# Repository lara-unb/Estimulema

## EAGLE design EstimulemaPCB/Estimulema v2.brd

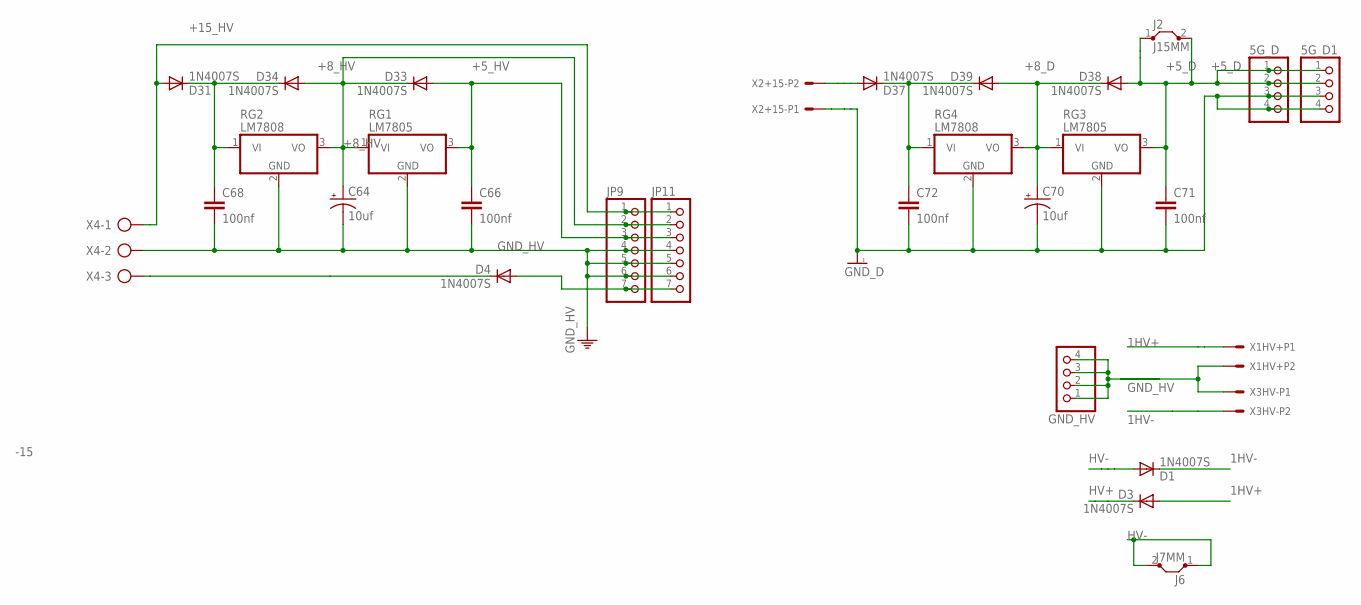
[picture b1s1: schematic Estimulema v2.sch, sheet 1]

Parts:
5G_D, 5G_D1: PINHD-1X4; 1X04
C64, C70: 10uf; E2-5
C66, C68, C71, C72: 100nf; C025-025X050
D1, D3, D4, D31, D33, D34, D37, D38, D39: 1N4007S; RESM4226X229
GND_HV: PINHD-1X4; 1X04
J2: J15MM; 15
J6: J7MM; 07
JP9, JP11: PINHD-1X7; 1X07
RG1, RG3: LM7805; TO220V
RG2, RG4: LM7808; TO220V
X1HV+, X2+15-, X3HV-: CONECTOR_5.08; CONECTOR_X2_5.08
X4: AK300/3

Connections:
1HV+: D3.AN (A), X1HV+.1
1HV-: D1.CA (C), X3HV-.2
+5_D: 5G_D.1, 5G_D.2, 5G_D1.1, 5G_D1.2, C71.1, D38.AN (A), J2.1, J2.2, RG3.3 (VO); also elsewhere on the board
+5_HV: C66.1, D33.AN (A), JP9.3, JP11.3, RG1.3 (VO); also elsewhere on the board
+8_D: C70.+, D38.CA (C), D39.AN (A), RG3.1 (VI), RG4.3 (VO)
+8_HV: C64.+, D33.CA (C), D34.AN (A), JP9.2, JP11.2, RG1.1 (VI), RG2.3 (VO)
+15_HV: D31.AN (A), JP9.1, JP11.1, X4.1; also elsewhere on the board
-15: D4.CA (C), X4.3
-15_HV: D4.AN (A), JP9.7, JP11.7; also elsewhere on the board
GND_D: 5G_D.3, 5G_D.4, 5G_D1.3, 5G_D1.4, C70.-, C71.2, C72.2, RG3.2 (GND), RG4.2 (GND), X2+15-.1; also elsewhere on the board
GND_HV: C64.-, C66.2, C68.2, GND_HV.1, GND_HV.2, GND_HV.3, GND_HV.4, JP9.4, JP9.5, JP9.6, JP11.4, JP11.5, JP11.6, RG1.2 (GND), RG2.2 (GND), X1HV+.2, X3HV-.1, X4.2; also elsewhere on the board
HV+: D3.CA (C); also elsewhere on the board
HV-: D1.AN (A), J6.1, J6.2; also elsewhere on the board
unnamed: D37.AN (A), X2+15-.2
unnamed: C68.1, D31.CA (C), D34.CA (C), RG2.1 (VI)
unnamed: C72.1, D37.CA (C), D39.CA (C), RG4.1 (VI)

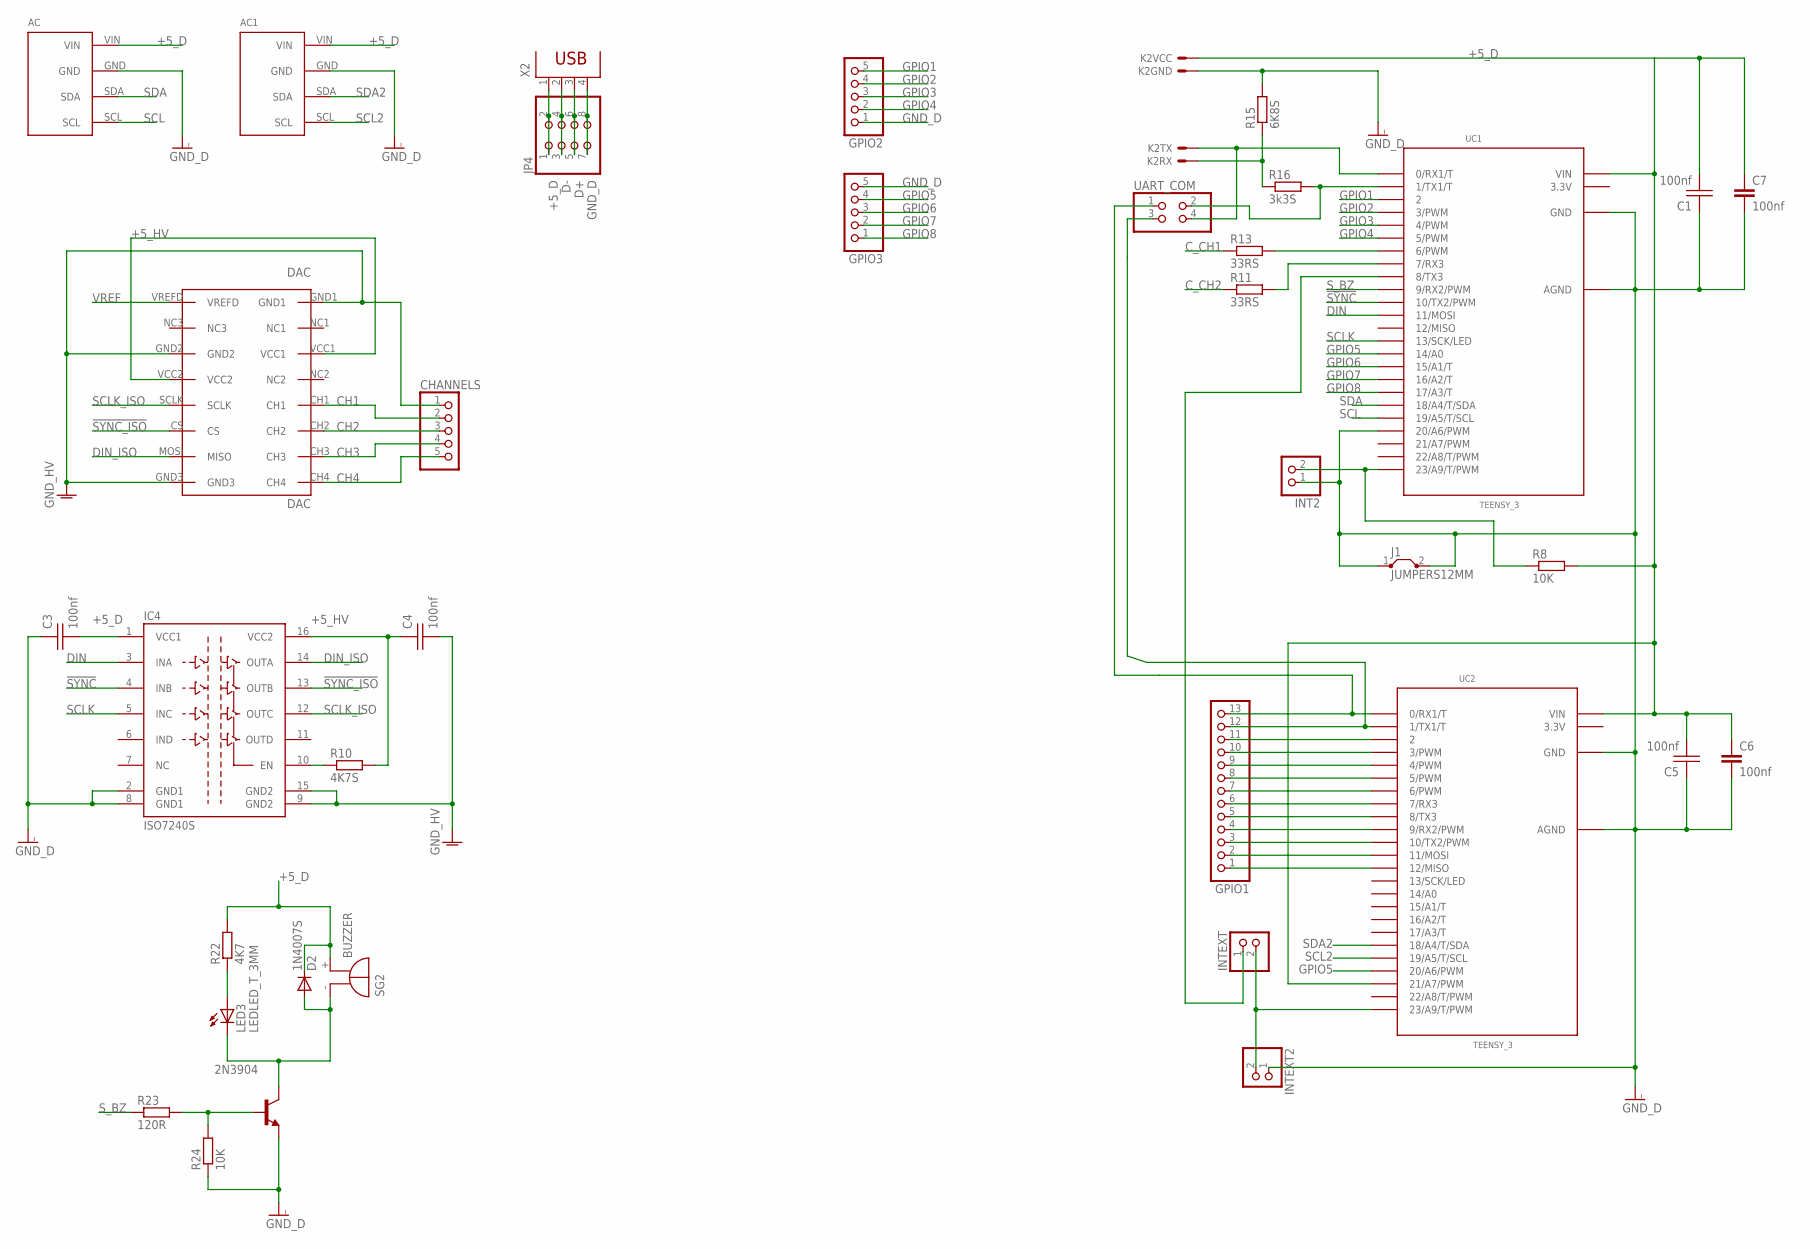
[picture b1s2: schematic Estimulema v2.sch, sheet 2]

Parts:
2N3904: 29-NPN-TO92-EBC; TO92-EBC
AC: CONECTOR_ACELEROMETRO_MPU6050CONECTOR_MPU6050; MPU6050
AC1: MPU6050
C1, C3, C4, C5: 100nf; CAP_CER_SMD-0805
C6, C7: 100nf; C025-025X050
CHANNELS: PINHD-1X5; 1X05
D2: 1N4007S; RESM4226X229
DAC: DAC; DACMOD_P
GPIO1: PINHD-1X13; 1X13
GPIO2, GPIO3: PINHD-1X5; 1X05
IC4: ISO7240S; SO-16DW
INT2: PINHD-1X2; 1X02
INTEXT, INTEXT2: PINHD-1X2; 1X02
J1: JUMPERS12MM; 12
JP4: PINHD-2X4; 2X04
K2: HC-06; CONECTOR_BTHC-06
LED3: LEDLED_T_3MM; LED3MM
R8, R24: 10K; RESISTENCIA_0805
R10: 4K7S; RESISTENCIA_0805
R11, R13: 33RS; RESISTENCIA_0805
R15: 6K8S; RESISTENCIA_0805
R16: 3k3S; RESISTENCIA_0805
R22: 4K7; RESISTENCIA_0805
R23: 120R; RESISTENCIA_0805
SG2: BUZZER
UART_COM: PINHD-2X2; 2X02
UC1, UC2: TEENSY_3; TEENSY_3.0-3.2_DIL
X2: PN61729

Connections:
3.3V: UC1.3.3V, UC2.3.3V
!SYNC: IC4.4 (INB), UC1.10 (10/TX2/PWM)
!SYNC_ISO: DAC.CS, IC4.13 (OUTB)
+5_D: AC.VIN, AC1.VIN, C1.2, C3.2, C5.2, C6.1, C7.1, D2.CA (C), IC4.1 (VCC1), JP4.1, JP4.2, K2.1, R8.2, R22.2, SG2.+ (-), UC1.VIN, UC2.21/A7 (21/A7/PWM), UC2.VIN, X2.1; also elsewhere on the board
+5_HV: C4.1, DAC.VCC1, DAC.VCC2, IC4.16 (VCC2), R10.2; also elsewhere on the board
CH1: CHANNELS.2, DAC.CH1; also elsewhere on the board
CH2: CHANNELS.3, DAC.CH2; also elsewhere on the board
CH3: CHANNELS.4, DAC.CH3
CH4: CHANNELS.5, DAC.CH4
C_15D: GPIO1.11, UC2.2
C_CH1: R13.1; also elsewhere on the board
C_CH2: R11.1; also elsewhere on the board
D+: JP4.5, JP4.6, X2.3
D-: JP4.3, JP4.4, X2.2
DIN: IC4.3 (INA), UC1.11 (11/MOSI)
DIN_ISO: DAC.MOSI (MISO), IC4.14 (OUTA)
GNDI: C3.1, IC4.2 (GND1), IC4.8 (GND1)
GND_D: 2N3904.E, AC.GND, AC1.GND, C1.1, C5.1, C6.2, C7.2, GPIO2.1, GPIO3.5, INT2.1, INTEXT2.1, J1.1, J1.2, JP4.7, JP4.8, K2.2, R15.2, R24.1, UC1.20/A6 (20/A6/PWM), UC1.AGND, UC1.GND, UC2.AGND, UC2.GND, X2.4; also elsewhere on the board
GND_HV: C4.2, CHANNELS.1, DAC.GND1, DAC.GND2, DAC.GND3, IC4.9 (GND2), IC4.15 (GND2); also elsewhere on the board
GPIO1: GPIO2.5, UC1.2
GPIO2: GPIO2.4, UC1.3 (3/PWM)
GPIO3: GPIO2.3, UC1.4 (4/PWM)
GPIO4: GPIO2.2, UC1.5 (5/PWM)
GPIO5: GPIO3.4, UC1.14/A0, UC2.20/A6 (20/A6/PWM)
GPIO6: GPIO3.3, UC1.15/A1 (15/A1/T)
GPIO7: GPIO3.2, UC1.16/A2 (16/A2/T)
GPIO8: GPIO3.1, UC1.17/A3 (17/A3/T)
unnamed: INTEXT.2, INTEXT2.2, UC2.23/A9 (23/A9/T/PWM)
unnamed: INTEXT.1, UC1.8 (8/TX3)
unnamed: GPIO1.13, UART_COM.1, UC2.0 (0/RX1/T)
unnamed: GPIO1.12, UART_COM.3, UC2.1 (1/TX1/T)
unnamed: GPIO1.10, UC2.3 (3/PWM)
unnamed: GPIO1.9, UC2.4 (4/PWM)
unnamed: GPIO1.8, UC2.5 (5/PWM)
unnamed: GPIO1.7, UC2.6 (6/PWM)
unnamed: GPIO1.6, UC2.7 (7/RX3)
unnamed: GPIO1.5, UC2.8 (8/TX3)
unnamed: GPIO1.4, UC2.9 (9/RX2/PWM)
unnamed: GPIO1.3, UC2.10 (10/TX2/PWM)
unnamed: GPIO1.2, UC2.11 (11/MOSI)
unnamed: GPIO1.1, UC2.12 (12/MISO)
unnamed: R16.2, UART_COM.2, UC1.1 (1/TX1/T)
unnamed: K2.3, UART_COM.4, UC1.0 (0/RX1/T)
unnamed: IC4.10 (EN), R10.1
unnamed: R13.2, UC1.6 (6/PWM)
unnamed: R11.2, UC1.7 (7/RX3)
unnamed: K2.4, R15.1, R16.1
unnamed: LED3.A, R22.1
unnamed: 2N3904.C, D2.AN (A), LED3.K (C), SG2.- (+)
unnamed: 2N3904.B, R23.2, R24.2
unnamed: INT2.2, R8.1, UC1.23/A9 (23/A9/T/PWM)
SCL: AC.SCL, UC1.19/A5 (19/A5/T/SCL)
SCL2: AC1.SCL, UC2.19/A5 (19/A5/T/SCL)
SCLK: IC4.5 (INC), UC1.13 (13/SCK/LED)
SCLK_ISO: DAC.SCLK, IC4.12 (OUTC)
SDA: AC.SDA, UC1.18/A4 (18/A4/T/SDA)
SDA2: AC1.SDA, UC2.18/A4 (18/A4/T/SDA)
S_BZ: R23.1, UC1.9 (9/RX2/PWM)
VREF: DAC.VREFD; also elsewhere on the board

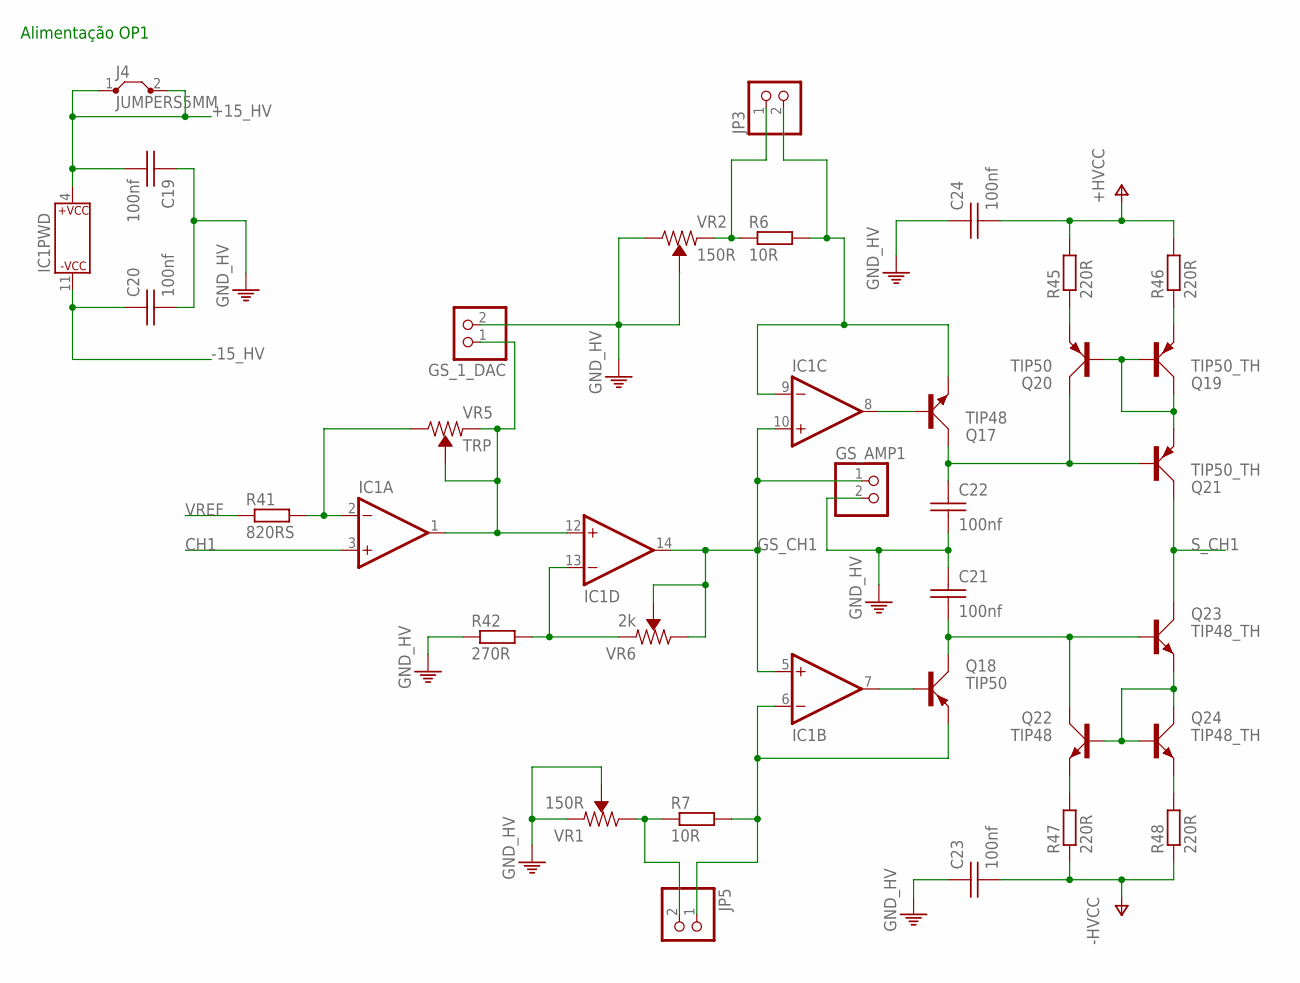
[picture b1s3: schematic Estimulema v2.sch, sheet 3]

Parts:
C19, C20: 100nf; CAP_CER_SMD-0805
C21, C22: 100nf; CAP_CER_2,54-5X5
C23, C24: 100nf; CAP_CER_16X7
GS_1_DAC: PINHD-1X2; 1X02
GS_AMP1: PINHD-1X2; 1X02
IC1: TL084DIL143D; DIL14
J4: JUMPERS5MM; 05
JP3, JP5: PINHD-1X2; 1X02
Q17, Q22: TIP48; TO220
Q18, Q20: TIP50; TO220
Q19, Q21: TIP50_TH; TO220
Q23, Q24: TIP48_TH; TO220
R6, R7: 10R; RESISTENCIA_0805
R41: 820RS; RESISTENCIA_0805
R42: 270R; RESISTENCIA_0805
R45, R46, R47, R48: 220R; 0204V
VR1, VR2: 150R; TRIMPOT-PTH-3386U
VR5: TRP; TRIMPOT-PTH-3386U
VR6: 2k; TRIMPOT-PTH-3386U

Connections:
+15_HV: C19.2, IC1.4 (P$V+), J4.1, J4.2; also elsewhere on the board
-15_HV: C20.1, IC1.11 (P$V-); also elsewhere on the board
CH1: IC1.3 (+IN); also elsewhere on the board
GND_HV: C19.1, C20.2, C21.1, C22.2, C23.1, C24.1, GS_1_DAC.2, GS_AMP1.2, R42.1, VR1.1 (CCW), VR1.2 (WIPER), VR2.2 (WIPER), VR2.3 (CW); also elsewhere on the board
GS_CH1: GS_AMP1.1, IC1.5 (+IN), IC1.10 (+IN), IC1.14 (OUT), VR6.2 (WIPER), VR6.3 (CW)
HV+: C24.2, R45.2, R46.2; also elsewhere on the board
HV-: C23.2, R47.1, R48.1; also elsewhere on the board
unnamed: JP5.2, R7.1, VR1.3 (CW)
unnamed: JP3.1, R6.1, VR2.1 (CCW)
unnamed: IC1.2 (-IN), R41.2, VR5.3 (CW)
unnamed: GS_1_DAC.1, IC1.1 (OUT), IC1.12 (+IN), VR5.1 (CCW), VR5.2 (WIPER)
unnamed: IC1.13 (-IN), R42.2, VR6.1 (CCW)
unnamed: IC1.9 (-IN), JP3.2, Q17.E, R6.2
unnamed: IC1.6 (-IN), JP5.1, Q18.E, R7.2
unnamed: C21.2, Q18.C, Q22.C, Q23.B
unnamed: C22.1, Q17.C, Q20.C, Q21.B
unnamed: Q20.E, R45.1
unnamed: Q19.E, R46.1
unnamed: Q19.B, Q19.C, Q20.B, Q21.E
unnamed: Q22.B, Q23.E, Q24.B, Q24.C
unnamed: Q22.E, R47.2
unnamed: Q24.E, R48.2
unnamed: IC1.8 (OUT), Q17.B
unnamed: IC1.7 (OUT), Q18.B
S_CH1: Q21.C, Q23.C; also elsewhere on the board
VREF: R41.1; also elsewhere on the board

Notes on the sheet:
Alimentação OP1

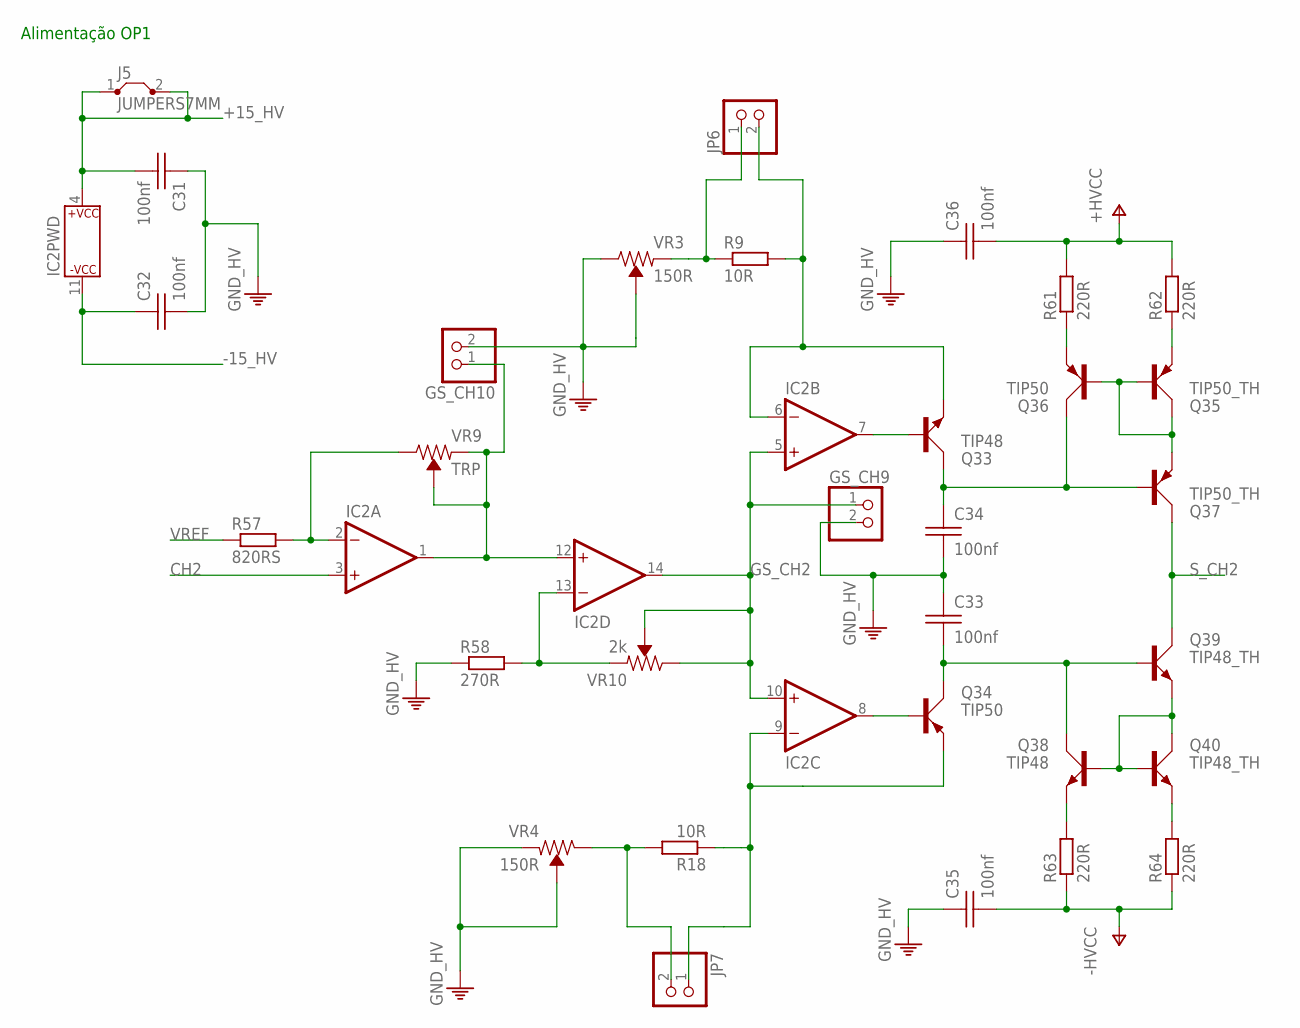
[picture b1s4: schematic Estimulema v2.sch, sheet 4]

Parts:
C31, C32: 100nf; CAP_CER_SMD-0805
C33, C34: 100nf; CAP_CER_2,54-5X5
C35, C36: 100nf; CAP_CER_16X7
GS_CH9, GS_CH10: PINHD-1X2; 1X02
IC2: TL084DIL143D; DIL14
J5: JUMPERS7MM; 07
JP6, JP7: PINHD-1X2; 1X02
Q33, Q38: TIP48; TO220
Q34, Q36: TIP50; TO220
Q35, Q37: TIP50_TH; TO220
Q39, Q40: TIP48_TH; TO220
R9, R18: 10R; RESISTENCIA_0805
R57: 820RS; RESISTENCIA_0805
R58: 270R; RESISTENCIA_0805
R61, R62, R63, R64: 220R; 0204V
VR3, VR4: 150R; TRIMPOT-PTH-3386U
VR9: TRP; TRIMPOT-PTH-3386U
VR10: 2k; TRIMPOT-PTH-3386U

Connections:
+15_HV: C31.2, IC2.4 (P$V+), J5.1, J5.2; also elsewhere on the board
-15_HV: C32.1, IC2.11 (P$V-); also elsewhere on the board
CH2: IC2.3 (+IN); also elsewhere on the board
GND_HV: C31.1, C32.2, C33.1, C34.2, C35.1, C36.1, GS_CH9.2, GS_CH10.2, R58.1, VR3.2 (WIPER), VR3.3 (CW), VR4.1 (CCW), VR4.2 (WIPER); also elsewhere on the board
GS_CH2: GS_CH9.1, IC2.5 (+IN), IC2.10 (+IN), IC2.14 (OUT), VR10.2 (WIPER), VR10.3 (CW)
HV+: C36.2, R61.2, R62.2; also elsewhere on the board
HV-: C35.2, R63.1, R64.1; also elsewhere on the board
unnamed: IC2.6 (-IN), JP6.2, Q33.E, R9.2
unnamed: JP6.1, R9.1, VR3.1 (CCW)
unnamed: JP7.2, R18.2, VR4.3 (CW)
unnamed: IC2.9 (-IN), JP7.1, Q34.E, R18.1
unnamed: IC2.2 (-IN), R57.2, VR9.3 (CW)
unnamed: GS_CH10.1, IC2.1 (OUT), IC2.12 (+IN), VR9.1 (CCW), VR9.2 (WIPER)
unnamed: IC2.13 (-IN), R58.2, VR10.1 (CCW)
unnamed: C33.2, Q34.C, Q38.C, Q39.B
unnamed: C34.1, Q33.C, Q36.C, Q37.B
unnamed: Q36.E, R61.1
unnamed: Q35.E, R62.1
unnamed: Q35.B, Q35.C, Q36.B, Q37.E
unnamed: Q38.B, Q39.E, Q40.B, Q40.C
unnamed: Q38.E, R63.2
unnamed: Q40.E, R64.2
unnamed: IC2.7 (OUT), Q33.B
unnamed: IC2.8 (OUT), Q34.B
S_CH2: Q37.C, Q39.C; also elsewhere on the board
VREF: R57.1; also elsewhere on the board

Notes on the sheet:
Alimentação OP1

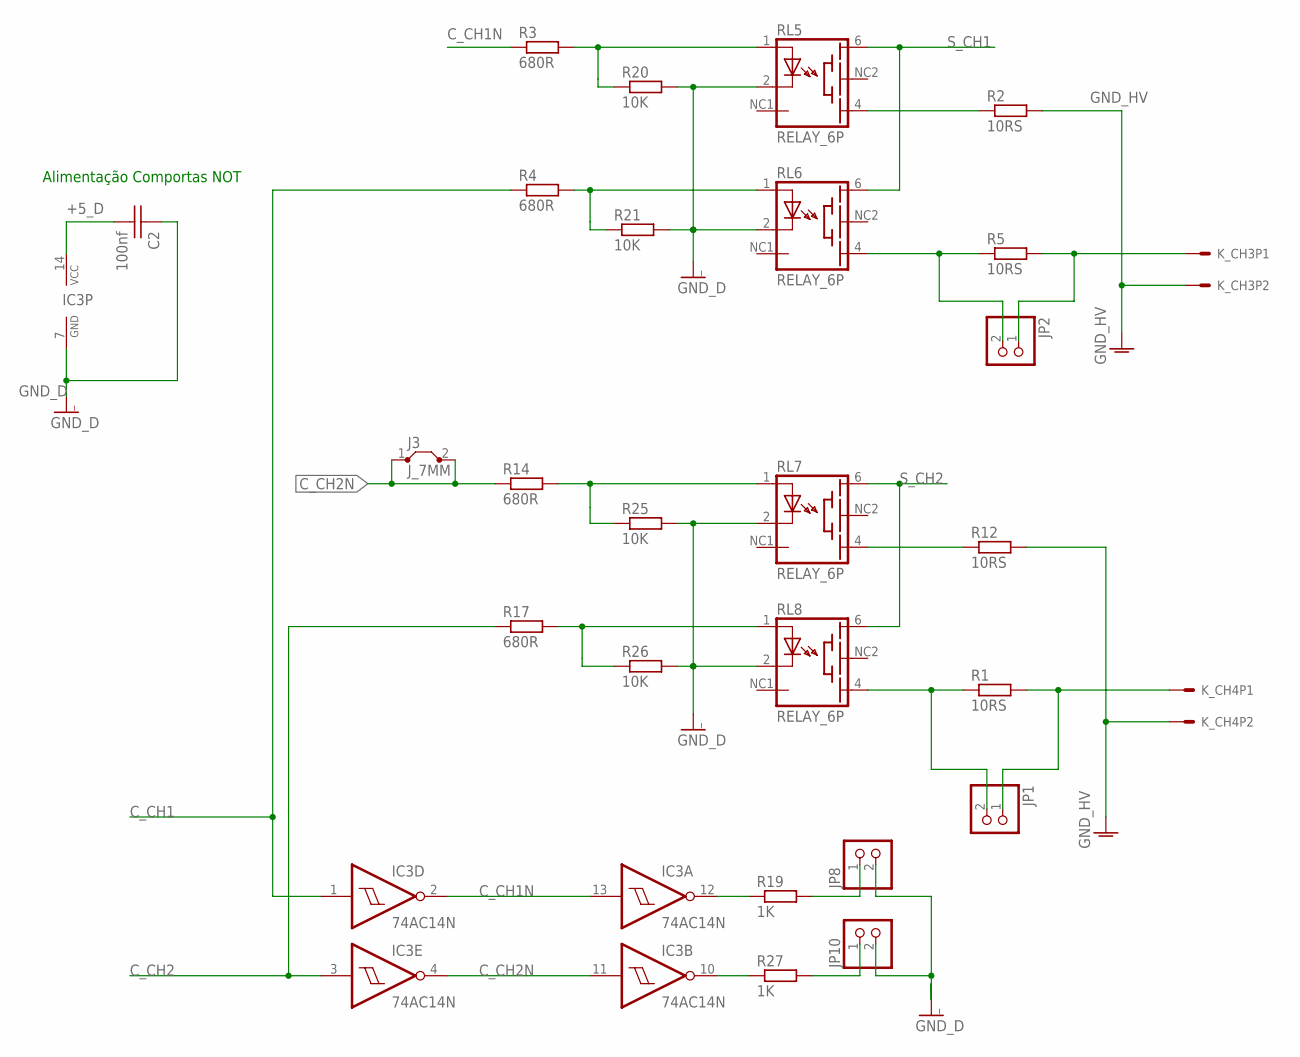
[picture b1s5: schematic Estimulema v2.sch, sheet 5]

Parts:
C2: 100nf; CAP_CER_SMD-0805
IC3: 74AC14N; DIL14
J3: J_7MM; 07
JP1, JP2, JP8, JP10: PINHD-1X2; 1X02
K_CH3, K_CH4: CONECTOR_5.08; CONECTOR_X2_5.08
R1, R5: 10RS; 0204/5
R2, R12: 10RS; 0617V
R3, R4, R14, R17: 680R; RESISTENCIA_0805
R19, R27: 1K; RESISTENCIA_0805
R20, R21, R25, R26: 10K; RESISTENCIA_0805
RL5, RL6, RL7, RL8: RELAY_6P; TS210

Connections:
+5_D: C2.2, IC3.14 (VCC); also elsewhere on the board
C_CH1: IC3.1 (I), R4.1; also elsewhere on the board
C_CH1N: IC3.2 (O), IC3.13 (I), R3.1
C_CH2: IC3.3 (I), R17.1; also elsewhere on the board
C_CH2N: IC3.4 (O), IC3.11 (I), J3.1, J3.2, R14.1
GND_D: C2.1, IC3.7 (GND), JP8.2, JP10.2, R20.2, R21.2, R25.2, R26.2, RL5.2 (C), RL6.2 (C), RL7.2 (C), RL8.2 (C); also elsewhere on the board
GND_HV: K_CH3.2, K_CH4.2, R2.2, R12.2; also elsewhere on the board
unnamed: R3.2, R20.1, RL5.1 (A)
unnamed: R4.2, R21.1, RL6.1 (A)
unnamed: R2.1, RL5.4 (EMI)
unnamed: JP2.2, R5.1, RL6.4 (EMI)
unnamed: R14.2, R25.1, RL7.1 (A)
unnamed: R17.2, R26.1, RL8.1 (A)
unnamed: R12.1, RL7.4 (EMI)
unnamed: JP2.1, K_CH3.1, R5.2
unnamed: JP1.1, K_CH4.1, R1.2
unnamed: JP1.2, R1.1, RL8.4 (EMI)
unnamed: JP8.1, R19.2
unnamed: IC3.12 (O), R19.1
unnamed: IC3.10 (O), R27.1
unnamed: JP10.1, R27.2
S_CH1: RL5.6 (BAS), RL6.6 (BAS); also elsewhere on the board
S_CH2: RL7.6 (BAS), RL8.6 (BAS); also elsewhere on the board

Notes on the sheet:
Alimentação Comportas NOT

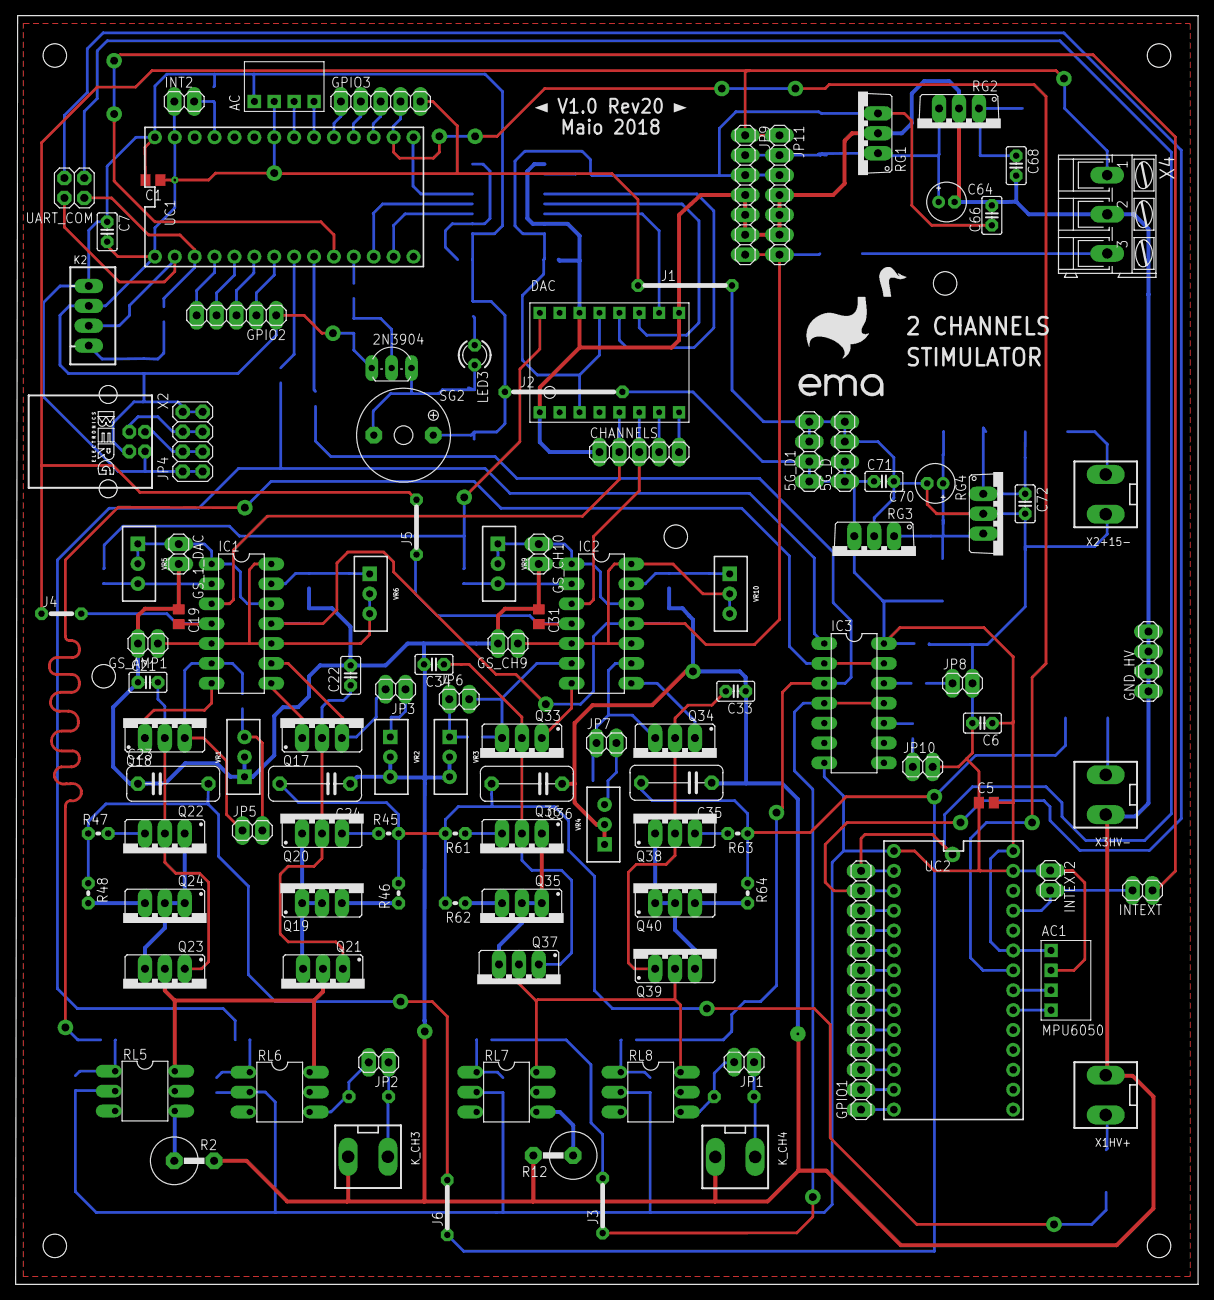
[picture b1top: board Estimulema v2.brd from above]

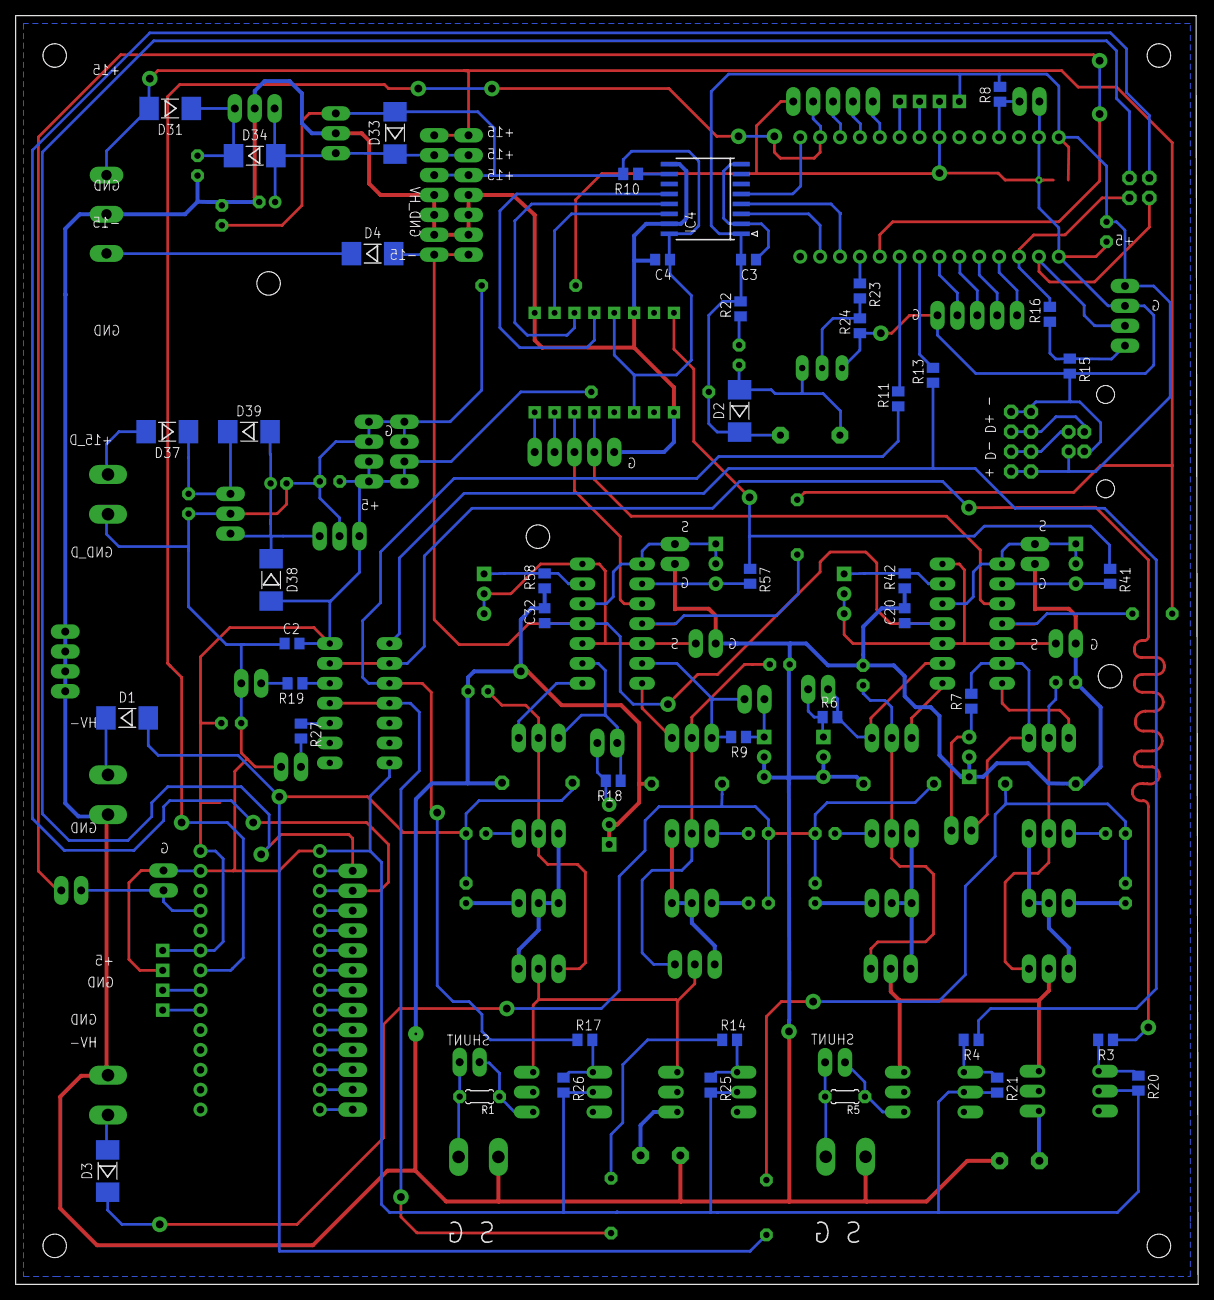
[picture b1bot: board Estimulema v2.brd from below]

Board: 2 copper layers, 151.0 x 162.0 mm, 158 parts (45 on the bottom side), 125 nets.

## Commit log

2018-04-16 First commit
    pronto primer hacer
2018-04-21 Comunication and Interface V1
    Communication work and finished interface for the first version
2018-04-23 testando nuevas funcionalidades
    implementando comunicaciony limites de therapy, Ton y TOff
2018-05-04 version antigua
    descartado esta version ahora est[a la version 2
2018-08-15 Colocando tudo de novo
2018-08-15 Última version funcionando
2018-08-15 Adicionando los INO del proyecto
    los ino usados actualmente son: EstimulemaV3_7-10-18.ino y MPU6050_raw_Mod.ino
2018-08-15 Adicionando el proyecto de la PCB
    adiciono el proyecto final hasta la fecha
2018-08-17 Add xls
    for test performance of estimulema
2018-08-20 Actualizacion
    Correcion de bugs, en la interface del py, problema boton de emergencia
2018-08-26 Actualizacion nuevos inclusiones
    inclusion del buzer
2018-08-27 Teste desempenho Dualpex
    los archivos csv estan en el archivo comprimido
2018-08-27 version en PDF
    PDF version
2018-08-30 Adicion de nuevas funcionalidades
    Furon adicionados:
    *- comunicacion serial entre stim y accel Serial1
    *- NUevo protocolo de comunicacion entre Teensys
    *- conteo de minutos en la interface
    *- modificacion de la GUI para colocar inicio y fin del teste de reobase
    *- modificaciones hechas tanto en los ino como en la py
2018-09-06 Nueva version del estimulema ino
    Version v4 con rampa algunos errores por arreglar
2018-09-12 ramp ini y fin
    adicionando dos rampas de inicio y fin
2018-09-12 Actualizacion de PCB
    Version corregida con todo
2018-09-16 Teste desempenho Tens-Fes HTM
    testes de desempenho
2018-09-26 Version final estimulema
    con ch1 funcionando con rampa, actualizado pcb y nueva version de estimula a la fecha, ademas de algunos modelos 3d
2018-10-09 update pcb estimulema v2
    cerregidos alguns errores que tenia la pcb
2018-10-09 New version eagle 9.2
    arreglando algunas cosas
2018-10-09 last version pcb file
    ultima version pcb
2018-10-11 Actualizaciones de ino y py
    algunas pequenhas modificaciones
2018-10-31 Treinamento y acel
    Ahora el stim ino y el diag and train pueden capturar datos del entrenamiento al igual que en el test de exitabilidad
2018-11-08 update pcb y ino para teste calibracion dac
2018-11-09 correciones de errores captura de acelerometro en secion de entrenamiento
    se corrigieron errores de generacion de archivo y parada de captura de datos
2019-04-16 final version working, teste OK!!
    Updates:
    1. Estimulema firmware:
    beep feature was remove of stim function
    Cronaxie: this function was remove of firmware and instead it was placed the calibration function for activate the accelerate acquisition.
    Other small fixes.
    2. Accel firmware: updates in serial communications and add functions for data flow control
2019-04-16 Two version of control of Stimulema
    1. Estimulema GUI
    2. Test GUI (excitability test and stimulation control)
2019-04-27 Atualização pcb e tese
2019-06-04 Modificaçoes GUI e Testes de Genesys
    Teste de desempenho Genesys e modificaciones del la intyerface de GUI
2019-06-04 Version Funcionando del Stimulema
    Diag and Train OK
2019-08-27 testes de desempenho
    libro com testes de desempenho
2019-08-27 version final teste fial
    archivos y modificaciones finales teste ext.
